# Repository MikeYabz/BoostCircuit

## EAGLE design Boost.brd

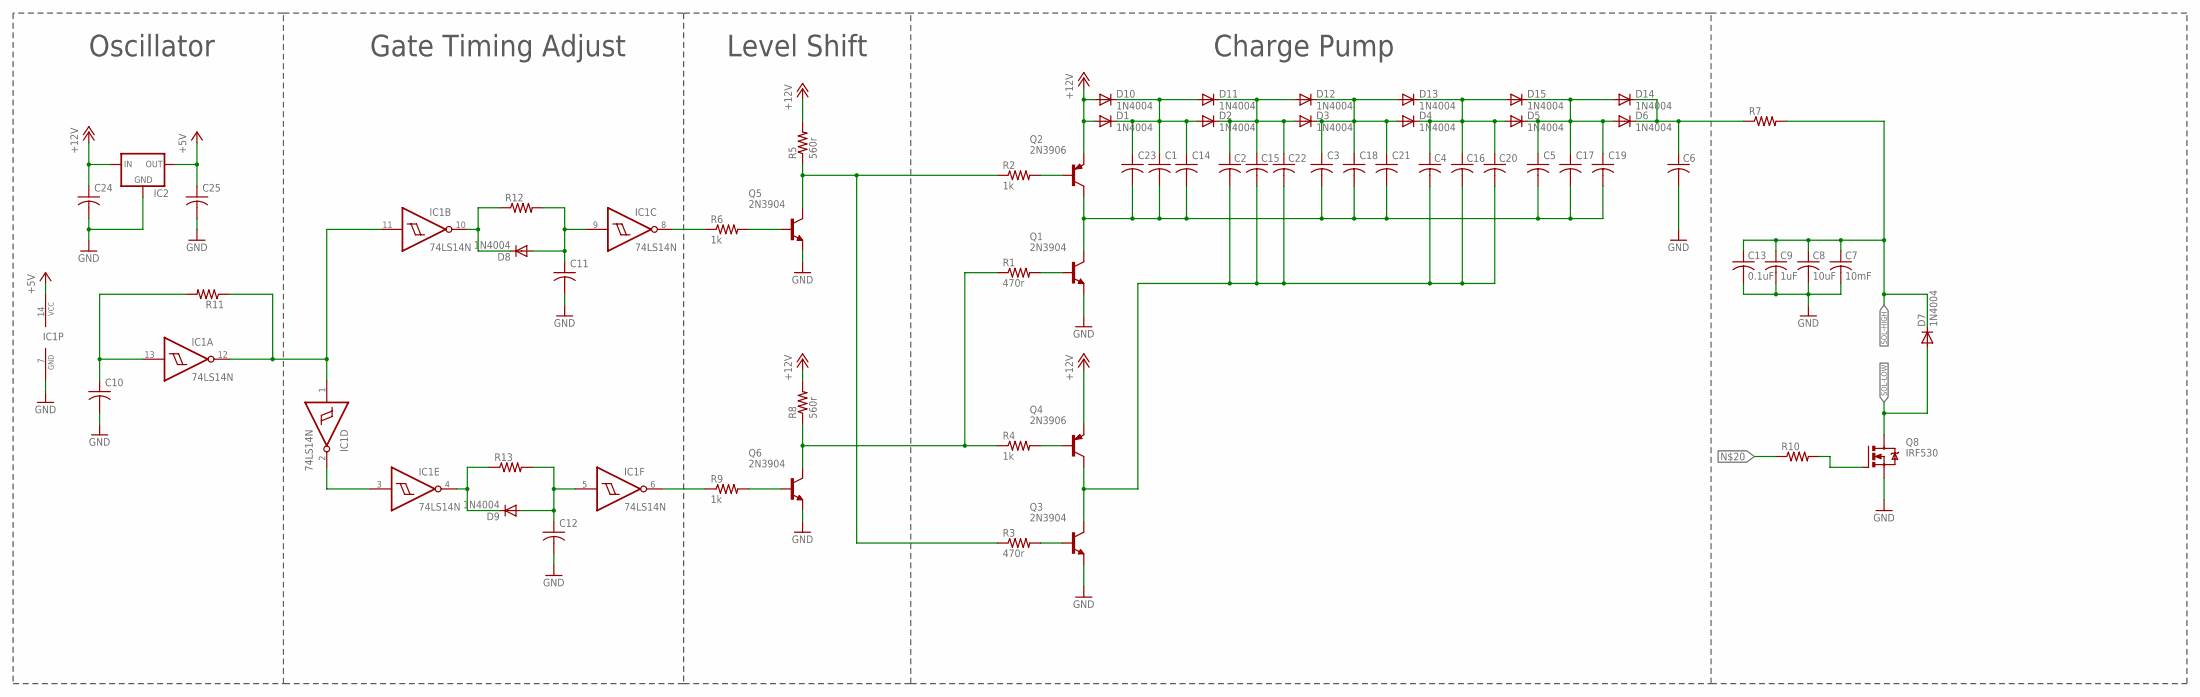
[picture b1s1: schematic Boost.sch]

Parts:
C1, C2, C3, C4, C5, C6, C10, C11, C12, C14, C15, C16, C17, C18, C19, C20, C21, C22, C23, C24, C25: C-US050-024X044; C050-024X044
C7: 10mF; C050-024X044
C8: 10uF; C050-024X044
C9: 1uF; C050-024X044
C13: 0.1uF; C050-024X044
D1, D2, D3, D4, D5, D6, D7, D8, D9, D10, D11, D12, D13, D14, D15: 1N4004; DO41-10
IC1: 74LS14N; DIL14
IC2: 78XXS
Q1, Q3, Q5, Q6: 2N3904; TO92
Q2, Q4: 2N3906; TO92
Q8: IRF530; TO220BV
R1, R3: 470r; 0207/10
R2, R4, R6, R9: 1k; 0207/10
R5, R8: 560r; 0207/10
R7, R10, R11, R12, R13: R-US_0207/10; 0207/10

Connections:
+5V: C25.1, IC1.14 (VCC), IC2.OUT
+5V1: C2.1, C15.1, C22.1, D2.C, D3.A, D11.C, D12.A
+12V: C24.1, D1.A, D10.A, IC2.IN, Q2.3 (E), Q4.3 (E), R5.2, R8.2
GND: C6.2, C7.2, C8.2, C9.2, C10.2, C11.2, C12.2, C13.2, C24.2, C25.2, IC1.7 (GND), IC2.GND, Q1.3 (E), Q3.3 (E), Q5.3 (E), Q6.3 (E), Q8.S
unnamed: Q5.1 (C), R2.1, R3.1, R5.1
unnamed: C1.1, C14.1, C23.1, D1.C, D2.A, D10.C, D11.A
unnamed: Q6.1 (C), R1.1, R4.1, R8.1
unnamed: Q1.2 (B), R1.2
unnamed: Q2.2 (B), R2.2
unnamed: Q5.2 (B), R6.2
unnamed: C3.1, C18.1, C21.1, D3.C, D4.A, D12.C, D13.A
unnamed: C4.1, C16.1, C20.1, D4.C, D5.A, D13.C, D15.A
unnamed: C5.1, C17.1, C19.1, D5.C, D6.A, D14.A, D15.C
unnamed: C6.1, D6.C, D14.C, R7.1
unnamed: C1.2, C3.2, C5.2, C14.2, C17.2, C18.2, C19.2, C21.2, C23.2, Q1.1 (C), Q2.1 (C)
unnamed: Q3.2 (B), R3.2
unnamed: Q4.2 (B), R4.2
unnamed: IC1.8 (O), R6.1
unnamed: Q6.2 (B), R9.2
unnamed: IC1.6 (O), R9.1
unnamed: Q8.G, R10.2
unnamed: IC1.1 (I), IC1.11 (I), IC1.12 (O), R11.1
unnamed: C10.1, IC1.13 (I), R11.2
unnamed: C11.1, D8.A, IC1.9 (I), R12.2
unnamed: D8.C, IC1.10 (O), R12.1
unnamed: C12.1, D9.A, IC1.5 (I), R13.2
unnamed: D9.C, IC1.4 (O), R13.1
unnamed: IC1.2 (O), IC1.3 (I)
unnamed: C2.2, C4.2, C15.2, C16.2, C20.2, C22.2, Q3.1 (C), Q4.1 (C)
SOL-HIGH: C7.1, C8.1, C9.1, C13.1, D7.C, R7.2
SOL-LOW: D7.A, Q8.D

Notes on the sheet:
Oscillator
Gate Timing Adjust
Level Shift
Charge Pump

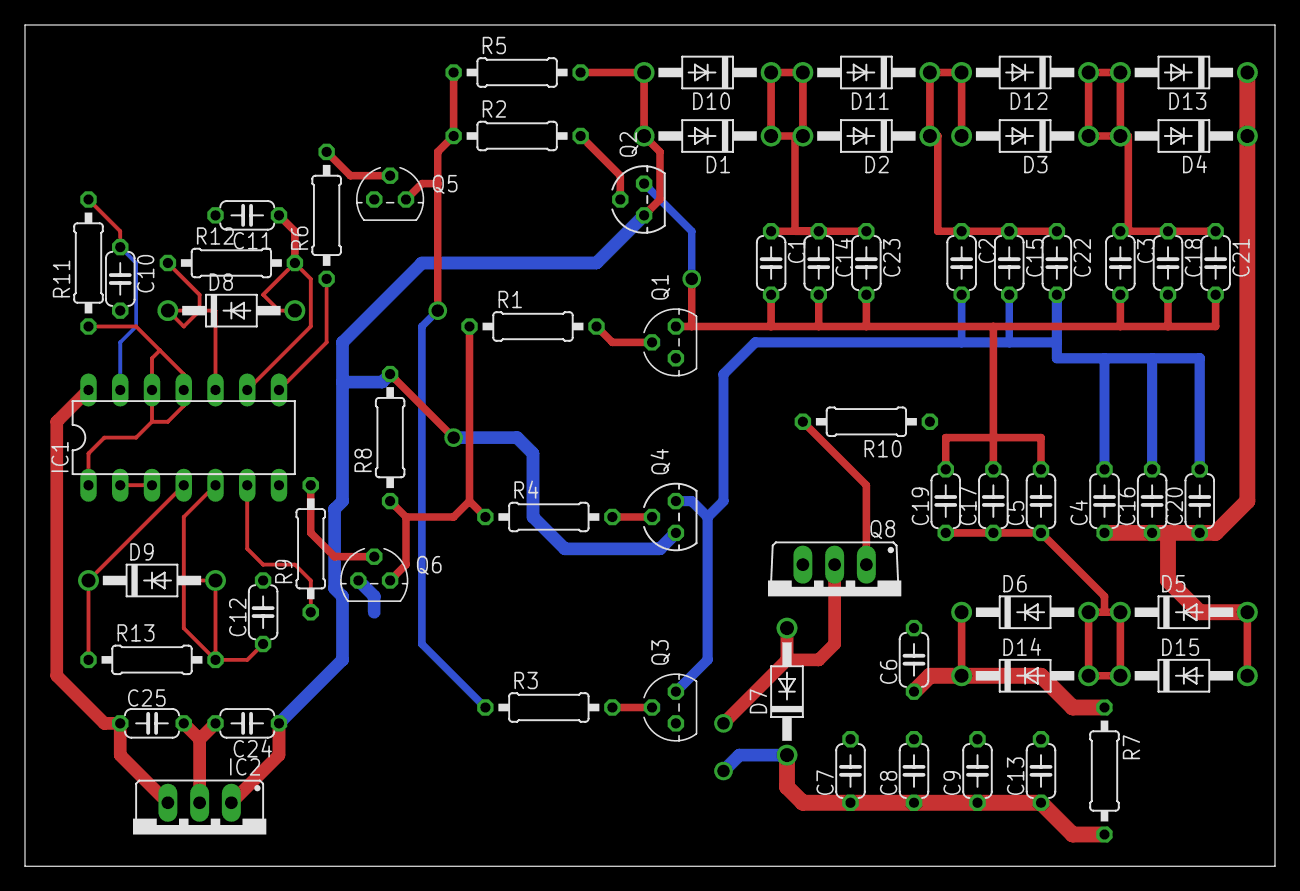
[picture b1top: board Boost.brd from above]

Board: 2 copper layers, 100.0 x 67.3 mm, 62 parts (0 on the bottom side), 31 nets.

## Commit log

2019-08-06 made circuit better, added more satges and driver
2019-10-08 board work
2019-10-08 board design
